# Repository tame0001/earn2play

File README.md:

# Earn2Play

I know I am a game addicted, I cannot hold myself accountable about playing time.
Stop playing completely will be too extreme.
So, I create a tracking system that will count how much time you spend on the things you suppose to do.
Then calculate time you can play game (or your favorite activities).

# Note to myself
- Complete design specification for timer circuit version 1 [link](circuit/timer%20v1/README.md)

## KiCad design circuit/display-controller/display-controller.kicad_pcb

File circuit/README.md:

This folder contains circuit design using KiCAD.

# 7-Segment Display

Each segment has 20 LEDs that draw 5mA each.
So, the total current drawn by a segment is 20 x 5mA = 100mA
And each digit will draw 7 x 100mA = 700mA

There will be 4 digits on the display, so the total current drawn will be 4 x 700mA = 2.8A
The power source will be 5V 3A.

## PCBA vs Manual

| Component | DigiKey | JLCPCB |
| --------- | ------- | ------ |
| LED       |         |
| Resistor  |         |
| Capacitor |         |

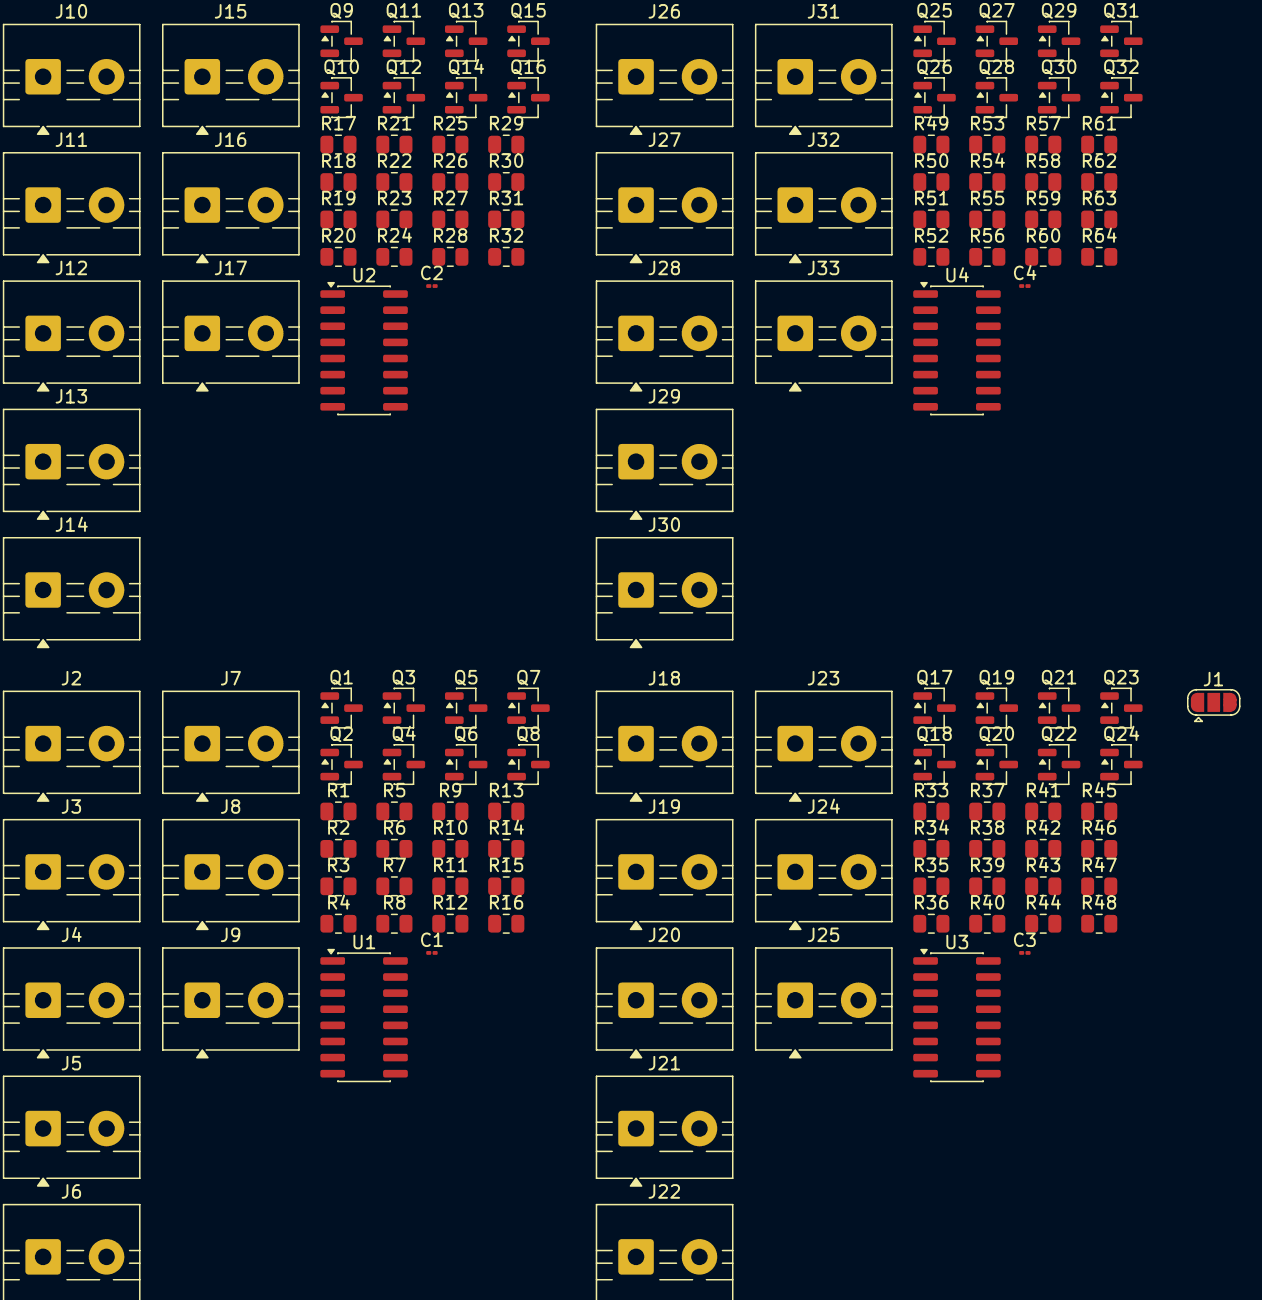
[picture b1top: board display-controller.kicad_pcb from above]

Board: 2 copper layers, 137 parts (0 on the bottom side), 102 nets, no tracks yet.

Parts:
C1, C2, C3, C4: 0.1 μF; C_01005_0402Metric
J1: Conn_01x03_Pin; SolderJumper-3_P1.3mm_Open_RoundedPad1.0x1.5mm
J2, J3, J4, J5, J6, J7, J8, J9, J10, J11, J12, J13, J14, J15, J16, J17, J18, J19, J20, J21, J22, J23, J24, J25, J26, J27, J28, J29, J30, J31, J32, J33: Screw_Terminal_01x02; TerminalBlock_MaiXu_MX126-5.0-02P_1x02_P5.00mm
Q1, Q2, Q3, Q4, Q5, Q6, Q7, Q8, Q9, Q10, Q11, Q12, Q13, Q14, Q15, Q16, Q17, Q18, Q19, Q20, Q21, Q22, Q23, Q24, Q25, Q26, Q27, Q28, Q29, Q30, Q31, Q32: AO3400; SOT-23
R1, R2, R5, R6, R9, R10, R13, R14, R17, R18, R21, R22, R25, R26, R29, R30, R33, R34, R37, R38, R41, R42, R45, R46, R49, R50, R53, R54, R57, R58, R61, R62: 10kΩ; R_0805_2012Metric
R3, R4, R7, R8, R11, R12, R15, R16, R19, R20, R23, R24, R27, R28, R31, R32, R35, R36, R39, R40, R43, R44, R47, R48, R51, R52, R55, R56, R59, R60, R63, R64: 100Ω; R_0805_2012Metric
U1, U2, U3, U4: 74HC595; SOIC-16_3.9x9.9mm_P1.27mm

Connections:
+5V: J1.1, J2.1, J3.1, J4.1, J5.1, J6.1, J7.1, J8.1, J9.1, J10.1, J11.1, J12.1, J13.1, J14.1, J15.1, J16.1, J17.1, J18.1, J19.1, J20.1, J21.1, J22.1, J23.1, J24.1, J25.1, J26.1, J27.1, J28.1, J29.1, J30.1, J31.1, J32.1, J33.1
/Digit-1/D0: R2.1, R4.1, U1.15 (QA)
/Digit-1/D1: R1.1, R3.1, U1.1 (QB)
/Digit-1/D2: R6.1, R8.1, U1.2 (QC)
/Digit-1/D3: R5.1, R7.1, U1.3 (QD)
/Digit-1/D4: R10.1, R12.1, U1.4 (QE)
/Digit-1/D5: R9.1, R11.1, U1.5 (QF)
/Digit-1/D6: R14.1, R16.1, U1.6 (QG)
/Digit-1/D7: R13.1, R15.1, U1.7 (QH)
/Digit-1/DOUT: U1.9 (QH'), U2.14 (SER)
/Digit-2/D0: R18.1, R20.1, U2.15 (QA)
/Digit-2/D1: R17.1, R19.1, U2.1 (QB)
/Digit-2/D2: R22.1, R24.1, U2.2 (QC)
/Digit-2/D3: R21.1, R23.1, U2.3 (QD)
/Digit-2/D4: R26.1, R28.1, U2.4 (QE)
/Digit-2/D5: R25.1, R27.1, U2.5 (QF)
/Digit-2/D6: R30.1, R32.1, U2.6 (QG)
/Digit-2/D7: R29.1, R31.1, U2.7 (QH)
/Digit-2/DOUT: U2.9 (QH'), U3.14 (SER)
/Digit-3/D0: R34.1, R36.1, U3.15 (QA)
/Digit-3/D1: R33.1, R35.1, U3.1 (QB)
/Digit-3/D2: R38.1, R40.1, U3.2 (QC)
/Digit-3/D3: R37.1, R39.1, U3.3 (QD)
/Digit-3/D4: R42.1, R44.1, U3.4 (QE)
/Digit-3/D5: R41.1, R43.1, U3.5 (QF)
/Digit-3/D6: R46.1, R48.1, U3.6 (QG)
/Digit-3/D7: R45.1, R47.1, U3.7 (QH)
/Digit-3/DOUT: U3.9 (QH'), U4.14 (SER)
/Digit-4/D0: R50.1, R52.1, U4.15 (QA)
/Digit-4/D1: R49.1, R51.1, U4.1 (QB)
/Digit-4/D2: R54.1, R56.1, U4.2 (QC)
/Digit-4/D3: R53.1, R55.1, U4.3 (QD)
/Digit-4/D4: R58.1, R60.1, U4.4 (QE)
/Digit-4/D5: R57.1, R59.1, U4.5 (QF)
/Digit-4/D6: R62.1, R64.1, U4.6 (QG)
/Digit-4/D7: R61.1, R63.1, U4.7 (QH)
GND: C1.2, C2.2, C3.2, C4.2, Q1.2 (S), Q2.2 (S), Q3.2 (S), Q4.2 (S), Q5.2 (S), Q6.2 (S), Q7.2 (S), Q8.2 (S), Q9.2 (S), Q10.2 (S), Q11.2 (S), Q12.2 (S), Q13.2 (S), Q14.2 (S), Q15.2 (S), Q16.2 (S), Q17.2 (S), Q18.2 (S), Q19.2 (S), Q20.2 (S), Q21.2 (S), Q22.2 (S), Q23.2 (S), Q24.2 (S), Q25.2 (S), Q26.2 (S), Q27.2 (S), Q28.2 (S), Q29.2 (S), Q30.2 (S), Q31.2 (S), Q32.2 (S), R1.2, R2.2, R5.2, R6.2, R9.2, R10.2, R13.2, R14.2, R17.2, R18.2, R21.2, R22.2, R25.2, R26.2, R29.2, R30.2, R33.2, R34.2, R37.2, R38.2, R41.2, R42.2, R45.2, R46.2, R49.2, R50.2, R53.2, R54.2, R57.2, R58.2, R61.2, R62.2, U1.8 (GND), U1.13 (~OE), U2.8 (GND), U2.13 (~OE), U3.8 (GND), U3.13 (~OE), U4.8 (GND), U4.13 (~OE)
unnamed: J2.2, Q1.3 (D)
unnamed: J3.2, Q2.3 (D)
unnamed: J4.2, Q3.3 (D)
unnamed: J5.2, Q4.3 (D)
unnamed: J6.2, Q5.3 (D)
unnamed: J7.2, Q6.3 (D)
unnamed: J8.2, Q7.3 (D)
unnamed: J9.2, Q8.3 (D)
unnamed: J10.2, Q9.3 (D)
unnamed: J11.2, Q10.3 (D)
unnamed: J12.2, Q11.3 (D)
unnamed: J13.2, Q12.3 (D)
unnamed: J14.2, Q13.3 (D)
unnamed: J15.2, Q14.3 (D)
unnamed: J16.2, Q15.3 (D)
unnamed: J17.2, Q16.3 (D)
unnamed: J18.2, Q17.3 (D)
unnamed: J19.2, Q18.3 (D)
unnamed: J20.2, Q19.3 (D)
unnamed: J21.2, Q20.3 (D)
unnamed: J22.2, Q21.3 (D)
unnamed: J23.2, Q22.3 (D)
unnamed: J24.2, Q23.3 (D)
unnamed: J25.2, Q24.3 (D)
unnamed: J26.2, Q25.3 (D)
unnamed: J27.2, Q26.3 (D)
unnamed: J28.2, Q27.3 (D)
unnamed: J29.2, Q28.3 (D)
unnamed: J30.2, Q29.3 (D)
unnamed: J31.2, Q30.3 (D)
unnamed: J32.2, Q31.3 (D)
unnamed: J33.2, Q32.3 (D)
unnamed: Q1.1 (G), R3.2
unnamed: Q2.1 (G), R4.2
unnamed: Q3.1 (G), R7.2
unnamed: Q4.1 (G), R8.2
unnamed: Q5.1 (G), R11.2
unnamed: Q6.1 (G), R12.2
unnamed: Q7.1 (G), R15.2
unnamed: Q8.1 (G), R16.2
unnamed: Q9.1 (G), R19.2
unnamed: Q10.1 (G), R20.2
unnamed: Q11.1 (G), R23.2
unnamed: Q12.1 (G), R24.2
unnamed: Q13.1 (G), R27.2
unnamed: Q14.1 (G), R28.2
unnamed: Q15.1 (G), R31.2
unnamed: Q16.1 (G), R32.2
unnamed: Q17.1 (G), R35.2
unnamed: Q18.1 (G), R36.2
unnamed: Q19.1 (G), R39.2
unnamed: Q20.1 (G), R40.2
unnamed: Q21.1 (G), R43.2
unnamed: Q22.1 (G), R44.2
unnamed: Q23.1 (G), R47.2
unnamed: Q24.1 (G), R48.2
unnamed: Q25.1 (G), R51.2
unnamed: Q26.1 (G), R52.2
unnamed: Q27.1 (G), R55.2
unnamed: Q28.1 (G), R56.2
unnamed: Q29.1 (G), R59.2
unnamed: Q30.1 (G), R60.2
unnamed: Q31.1 (G), R63.2
unnamed: Q32.1 (G), R64.2
VCC: C1.1, C2.1, C3.1, C4.1, J1.2, U1.10 (~SRCLR), U1.16 (VCC), U2.10 (~SRCLR), U2.16 (VCC), U3.10 (~SRCLR), U3.16 (VCC), U4.10 (~SRCLR), U4.16 (VCC)

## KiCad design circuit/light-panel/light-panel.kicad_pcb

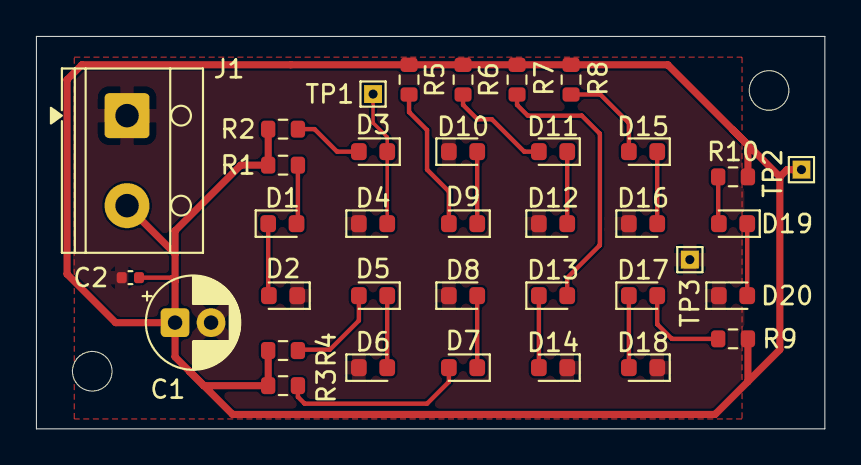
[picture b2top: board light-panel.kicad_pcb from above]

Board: 2 copper layers, 43.8 x 21.8 mm, 38 parts (0 on the bottom side), 22 nets.

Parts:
C1: 47uF 25V; CP_Radial_D5.0mm_P2.00mm
C2: 100nF 16V; C_0402_1005Metric
D1, D2, D3, D4, D5, D6, D7, D8, D9, D10, D11, D12, D13, D14, D15, D16, D17, D18, D19, D20: KT-0603R; LED_0603_1608Metric
H1, H2: MountingHole; MountingHole_2.2mm_M2
J1: Screw_Terminal_01x02; TerminalBlock_RND_205-00012_1x02_P5.00mm_Horizontal
R1, R2, R3, R4, R5, R6, R7, R8, R9, R10: 330Ω; R_0603_1608Metric
TP1, TP2, TP3: TestPoint_Probe; TestPoint_THTPad_1.0x1.0mm_Drill0.5mm

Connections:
+5V: C1.1, C2.1, J1.2, R1.1, R2.1, R3.1, R4.1, R5.1, R6.1, R7.1, R8.1, R9.1, R10.1, TP2.1 (1_1)
GND: C1.2, C2.2, D2.1 (K), D4.1 (K), D6.1 (K), D8.1 (K), D10.1 (K), D12.1 (K), D14.1 (K), D16.1 (K), D18.1 (K), D20.1 (K), J1.1, TP3.1 (1_1)
unnamed: D1.2 (A), R1.2
unnamed: D1.1 (K), D2.2 (A)
unnamed: D3.2 (A), R2.2
unnamed: D3.1 (K), D4.2 (A), TP1.1 (1_1)
unnamed: D5.2 (A), R3.2
unnamed: D5.1 (K), D6.2 (A)
unnamed: D7.2 (A), R4.2
unnamed: D7.1 (K), D8.2 (A)
unnamed: D9.2 (A), R5.2
unnamed: D9.1 (K), D10.2 (A)
unnamed: D11.2 (A), R6.2
unnamed: D11.1 (K), D12.2 (A)
unnamed: D13.2 (A), R7.2
unnamed: D13.1 (K), D14.2 (A)
unnamed: D15.2 (A), R8.2
unnamed: D15.1 (K), D16.2 (A)
unnamed: D17.2 (A), R9.2
unnamed: D17.1 (K), D18.2 (A)
unnamed: D19.2 (A), R10.2
unnamed: D19.1 (K), D20.2 (A)

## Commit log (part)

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2025-01-08 update config
2026-06-18 picked LED
2026-06-18 deactivate deploy workflow
2026-06-19 New 7-segment part
2026-06-23 Change LED current from 15mA to 5mA
2026-06-25 start layout
